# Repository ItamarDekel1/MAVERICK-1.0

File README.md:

# MAVERICK-1.0
MAVERICK 1.0: The first iteration of the flight controller, developed by Itamar Dekel, designed for drones and autonomous vehicles.

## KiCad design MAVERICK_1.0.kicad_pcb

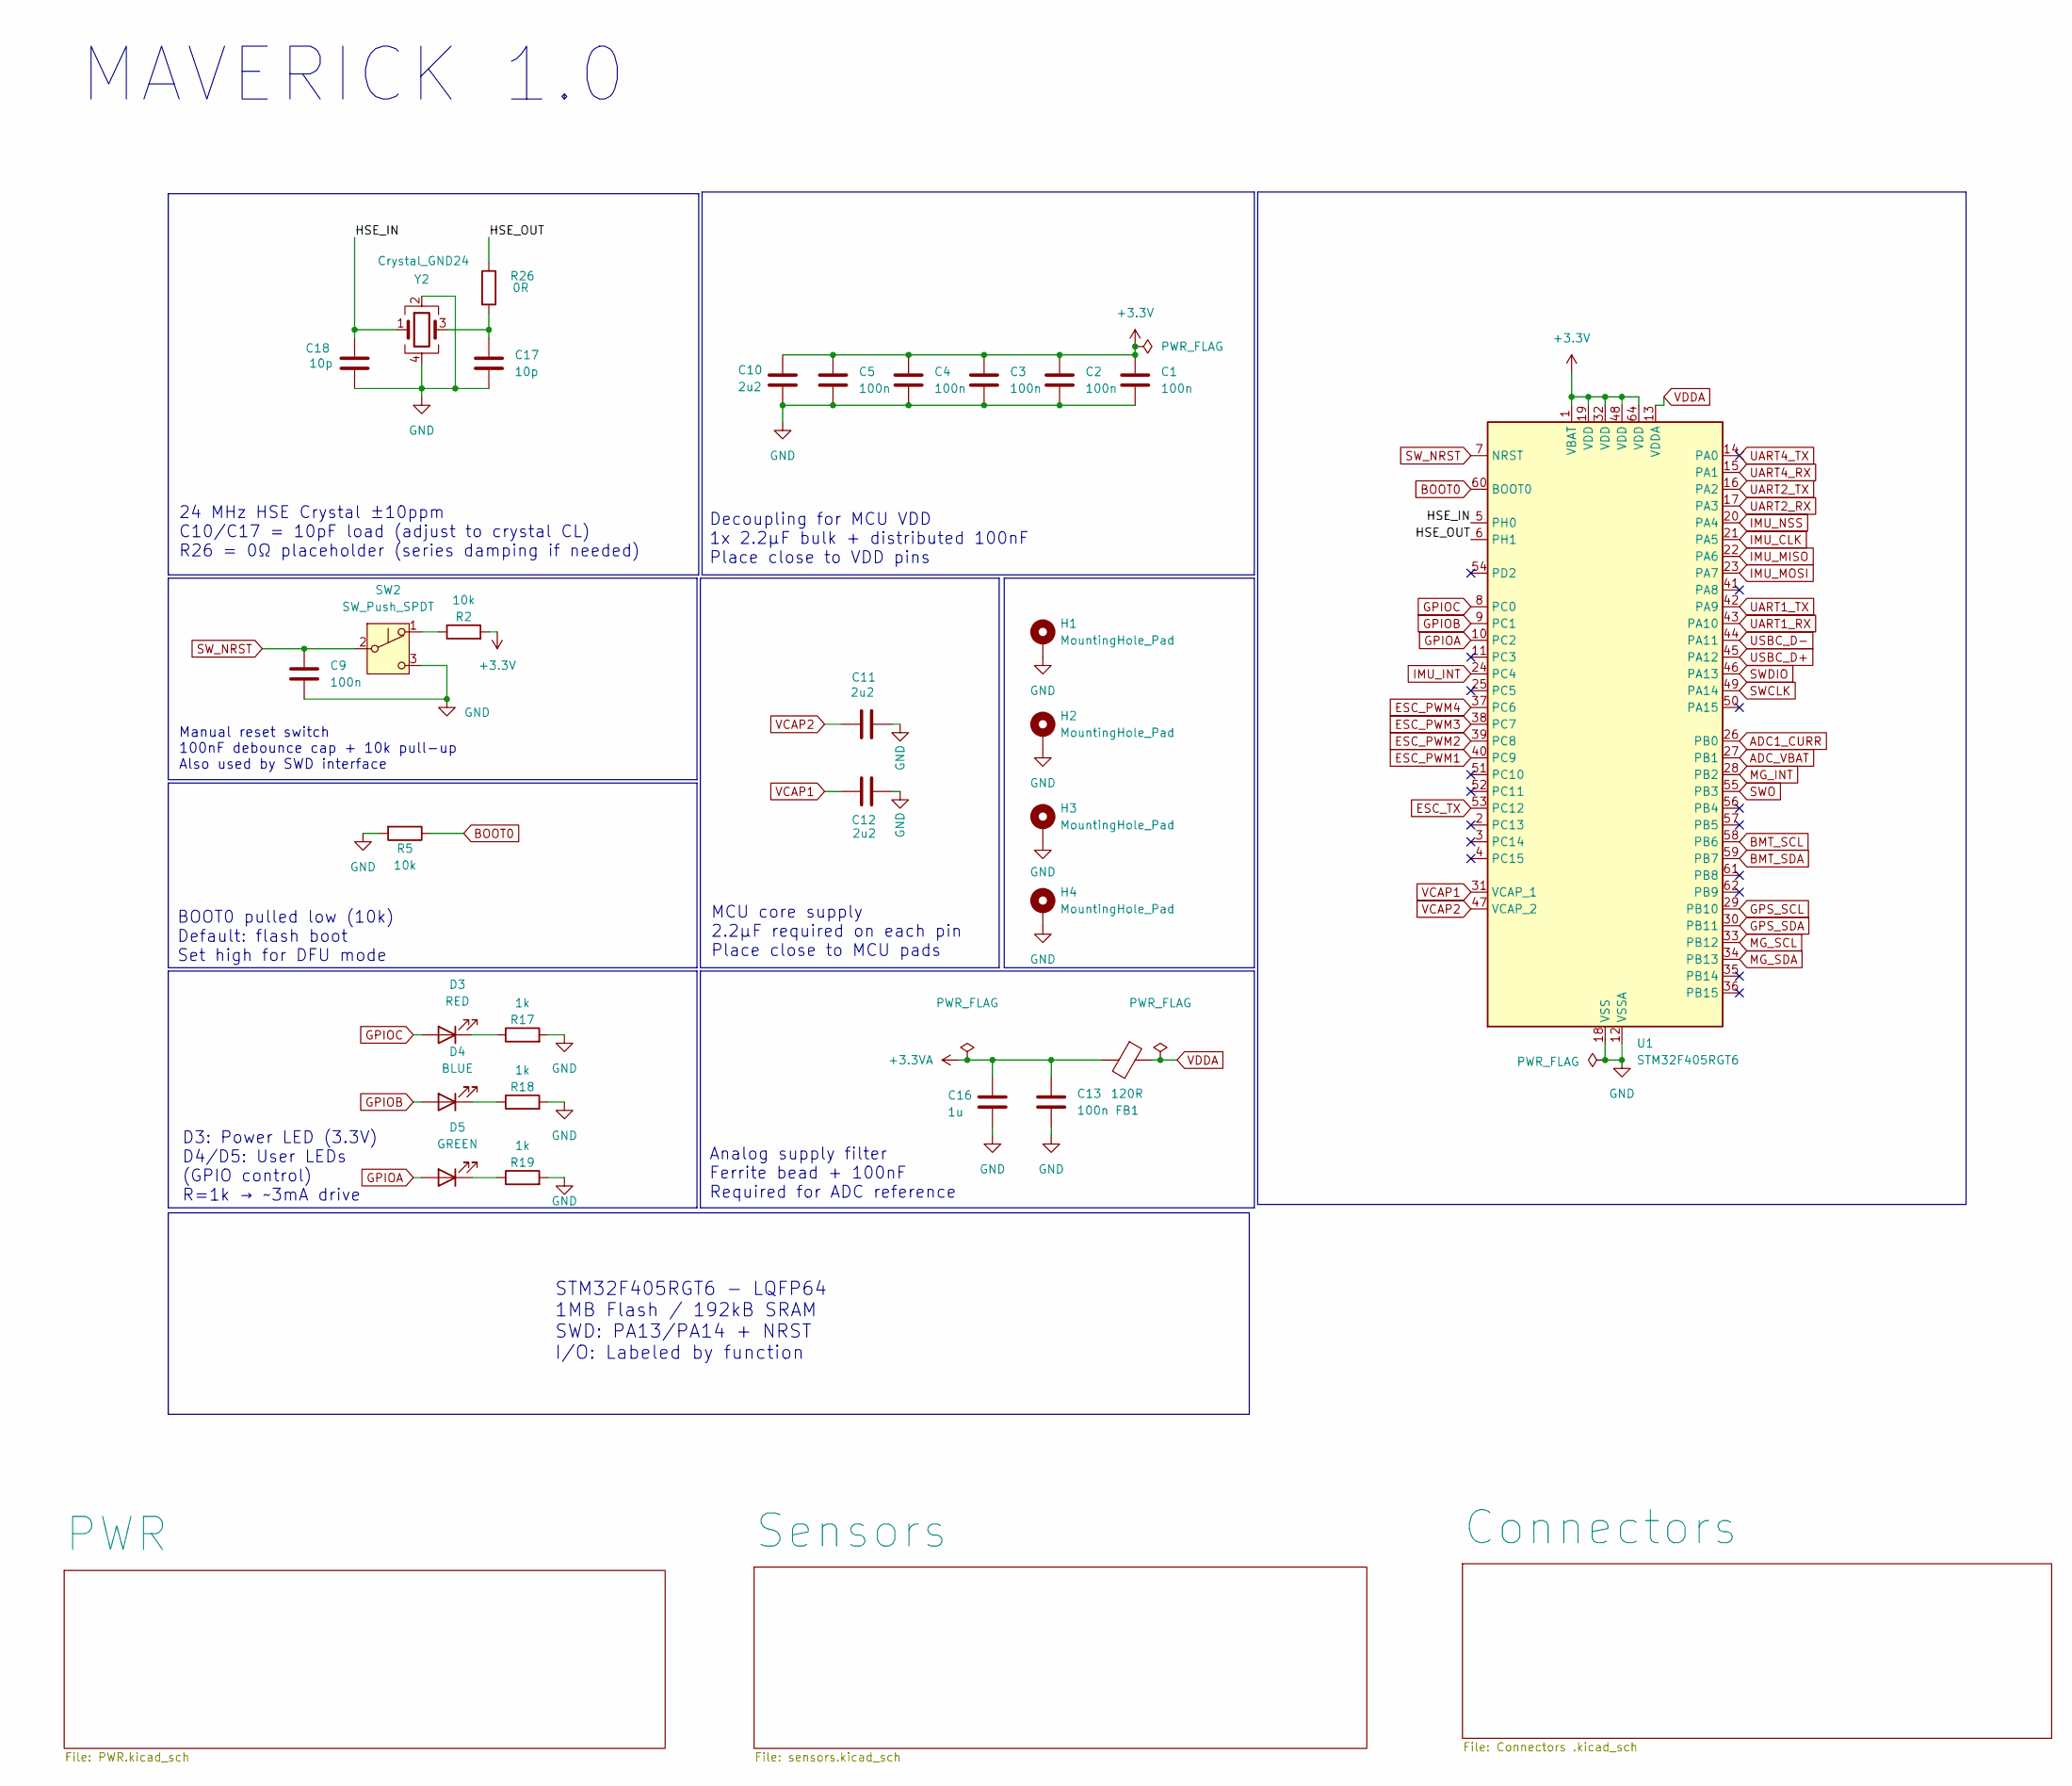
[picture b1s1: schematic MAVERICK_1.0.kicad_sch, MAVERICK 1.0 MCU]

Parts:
C1, C2, C3, C4, C5, C9, C13: 100n; C_0402_1005Metric
C10, C11, C12: 2u2; C_0603_1608Metric
C16: 1u; C_0402_1005Metric
C17, C18: 10p; C_0402_1005Metric
D3: RED; LED_0201_0603Metric
D4: BLUE; LED_0201_0603Metric
D5: GREEN; LED_0201_0603Metric
FB1: 120R; L_0402_1005Metric
H1, H2, H3, H4: MountingHole_Pad; MountingHole_2.2mm_M2_Pad_Via
R2, R5: 10k; R_0402_1005Metric
R17, R18, R19: 1k; R_0402_1005Metric
R26: 0R; R_0402_1005Metric
SW2: SW_Push_SPDT; SW_SPDT_PCM12
U1: STM32F405RGT6; LQFP-64_10x10mm_P0.5mm
Y2: Crystal_GND24; Crystal_SMD_3225-4Pin_3.2x2.5mm

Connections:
+3.3V: C1.1, C2.1, C3.1, C4.1, C5.1, C10.1, R2.2, U1.1 (VBAT), U1.19 (VDD), U1.32 (VDD), U1.48 (VDD), U1.64 (VDD); also elsewhere on the board
+3.3VA: C13.1, C16.1, FB1.2
/HSE_IN: C18.2, U1.5 (PH0), Y2.1
/HSE_OUT: R26.1, U1.6 (PH1)
ADC1_CURR: U1.26 (PB0); also elsewhere on the board
ADC_VBAT: U1.27 (PB1); also elsewhere on the board
BMT_SCL: U1.58 (PB6); also elsewhere on the board
BMT_SDA: U1.59 (PB7); also elsewhere on the board
BOOT0: R5.1, U1.60 (BOOT0)
ESC_PWM1: U1.40 (PC9); also elsewhere on the board
ESC_PWM2: U1.39 (PC8); also elsewhere on the board
ESC_PWM3: U1.38 (PC7); also elsewhere on the board
ESC_PWM4: U1.37 (PC6); also elsewhere on the board
ESC_TX: U1.53 (PC12); also elsewhere on the board
GND: C1.2, C2.2, C3.2, C4.2, C5.2, C9.1, C10.2, C11.2, C12.2, C13.2, C16.2, C17.1, C18.1, H1.1, H2.1, H3.1, H4.1, R5.2, R17.2, R18.2, R19.2, SW2.3 (C), U1.12 (VSSA), U1.18 (VSS), U1.63 (VSS), Y2.2, Y2.4; also elsewhere on the board
GPIOA: D5.2 (A), U1.10 (PC2)
GPIOB: D4.2 (A), U1.9 (PC1)
GPIOC: D3.2 (A), U1.8 (PC0)
GPS_SCL: U1.29 (PB10); also elsewhere on the board
GPS_SDA: U1.30 (PB11); also elsewhere on the board
IMU_CLK: U1.21 (PA5); also elsewhere on the board
IMU_INT: U1.24 (PC4); also elsewhere on the board
IMU_MISO: U1.22 (PA6); also elsewhere on the board
IMU_MOSI: U1.23 (PA7); also elsewhere on the board
IMU_NSS: U1.20 (PA4); also elsewhere on the board
MG_INT: U1.28 (PB2); also elsewhere on the board
MG_SCL: U1.33 (PB12); also elsewhere on the board
MG_SDA: U1.34 (PB13); also elsewhere on the board
unnamed: C17.2, R26.2, Y2.3
unnamed: D3.1 (K), R17.1
unnamed: D4.1 (K), R18.1
unnamed: D5.1 (K), R19.1
unnamed: R2.1, SW2.1 (A)
SWCLK: U1.49 (PA14); also elsewhere on the board
SWDIO: U1.46 (PA13); also elsewhere on the board
SWO: U1.55 (PB3); also elsewhere on the board
SW_NRST: C9.2, SW2.2 (B), U1.7 (NRST); also elsewhere on the board
UART1_RX: U1.43 (PA10); also elsewhere on the board
UART1_TX: U1.42 (PA9); also elsewhere on the board
UART2_RX: U1.17 (PA3); also elsewhere on the board
UART2_TX: U1.16 (PA2); also elsewhere on the board
UART4_RX: U1.15 (PA1); also elsewhere on the board
UART4_TX: U1.14 (PA0)
USBC_D+: U1.45 (PA12); also elsewhere on the board
USBC_D-: U1.44 (PA11); also elsewhere on the board
VCAP1: C12.1, U1.31 (VCAP_1)
VCAP2: C11.1, U1.47 (VCAP_2)
VDDA: FB1.1, U1.13 (VDDA)

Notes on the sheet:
STM32F405RGT6 - LQFP64 1MB Flash / 192kB SRAM SWD: PA13/PA14 + NRST I/O: Labeled by function
Manual reset switch 100nF debounce cap + 10k pull-up Also used by SWD interface
24 MHz HSE Crystal ±10ppm C10/C17 = 10pF load (adjust to crystal CL) R26 = 0Ω placeholder (series damping if needed)
MCU core supply 2.2µF required on each pin Place close to MCU pads
BOOT0 pulled low (10k) Default: flash boot Set high for DFU mode
MAVERICK 1.0
Decoupling for MCU VDD 1x 2.2µF bulk + distributed 100nF Place close to VDD pins
D3: Power LED (3.3V) D4/D5: User LEDs (GPIO control) R=1k → ~3mA drive
Analog supply filter Ferrite bead + 100nF Required for ADC reference

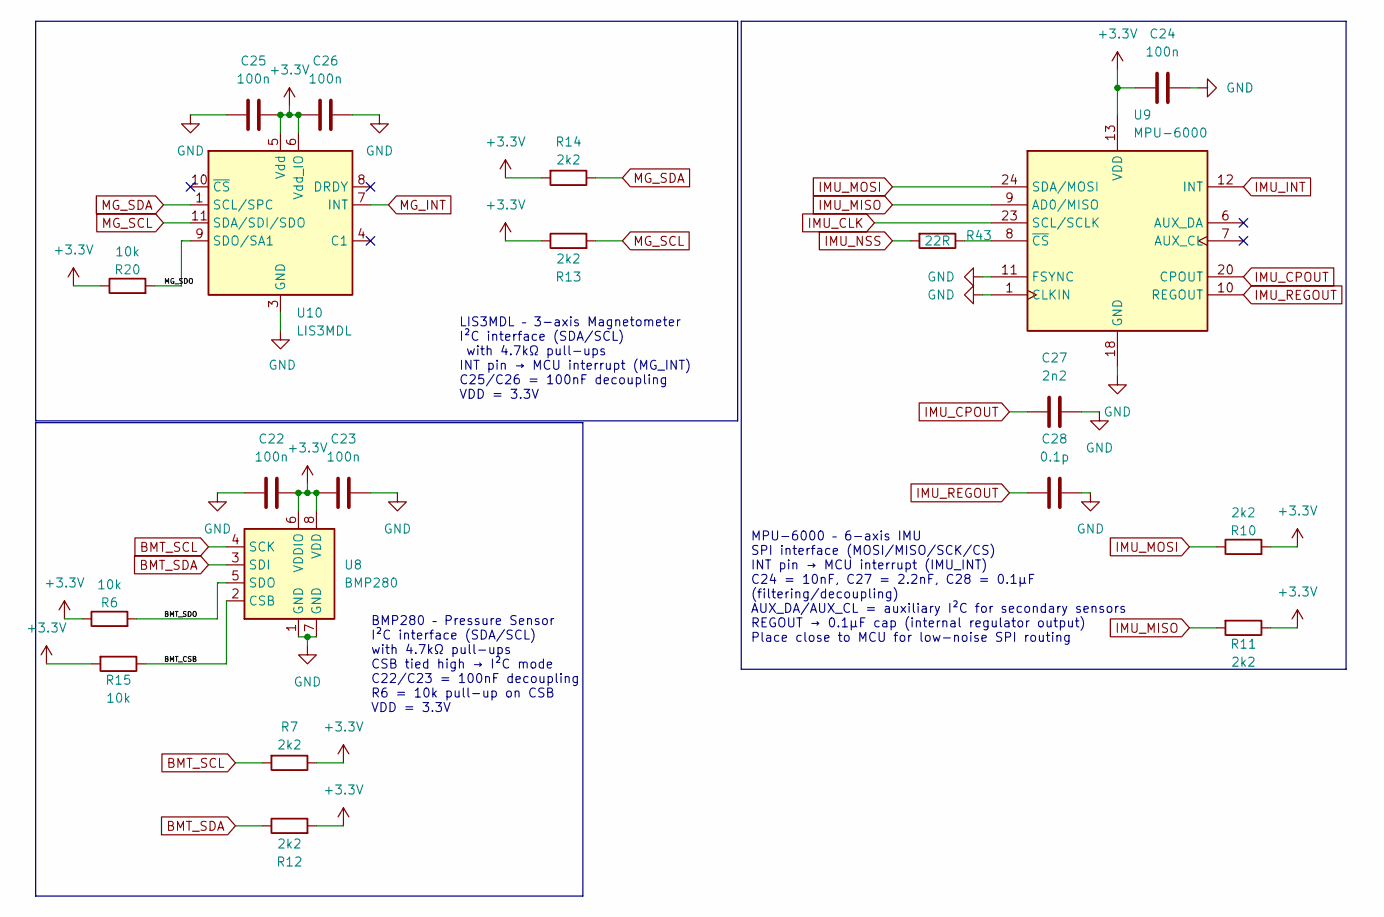
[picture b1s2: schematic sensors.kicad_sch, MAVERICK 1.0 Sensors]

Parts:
C22, C23, C24, C25, C26: 100n; C_0402_1005Metric
C27: 2n2; C_0603_1608Metric
C28: 0.1p; C_0402_1005Metric
R6, R15, R20: 10k; R_0402_1005Metric
R7, R10, R11, R12, R13, R14: 2k2; R_0402_1005Metric
R43: 22R; R_0402_1005Metric
U8: BMP280; Bosch_LGA-8_2x2.5mm_P0.65mm_ClockwisePinNumbering
U9: MPU-6000; InvenSense_QFN-24_4x4mm_P0.5mm
U10: LIS3MDL; LGA-12_2x2mm_P0.5mm

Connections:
+3.3V: C22.1, C23.2, C24.2, C25.1, C26.2, R6.1, R7.1, R10.2, R11.1, R12.2, R13.1, R14.2, R15.2, R20.1, U8.6 (VDDIO), U8.8 (VDD), U9.13 (VDD), U10.5 (Vdd), U10.6 (Vdd_IO); also elsewhere on the board
/Sensors/BMT_CSB: R15.1, U8.2 (CSB)
/Sensors/BMT_SDO: R6.2, U8.5 (SDO)
/Sensors/MG_SDO: R20.2, U10.9 (SDO/SA1)
BMT_SCL: R7.2, U8.4 (SCK); also elsewhere on the board
BMT_SDA: R12.1, U8.3 (SDI); also elsewhere on the board
GND: C22.2, C23.1, C24.1, C25.2, C26.1, C27.1, C28.1, U8.1 (GND), U8.7 (GND), U9.1 (CLKIN), U9.11 (FSYNC), U9.18 (GND), U10.2 (GND), U10.3 (GND), U10.12 (GND); also elsewhere on the board
IMU_CLK: U9.23 (SCL/SCLK); also elsewhere on the board
IMU_CPOUT: C27.2, U9.20 (CPOUT)
IMU_INT: U9.12 (INT); also elsewhere on the board
IMU_MISO: R11.2, U9.9 (AD0/MISO); also elsewhere on the board
IMU_MOSI: R10.1, U9.24 (SDA/MOSI); also elsewhere on the board
IMU_NSS: R43.2; also elsewhere on the board
IMU_REGOUT: C28.2, U9.10 (REGOUT)
MG_INT: U10.7 (INT); also elsewhere on the board
MG_SCL: R13.2, U10.11 (SDA/SDI/SDO); also elsewhere on the board
MG_SDA: R14.1, U10.1 (SCL/SPC); also elsewhere on the board
unnamed: R43.1, U9.8 (~CS)

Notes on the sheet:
MPU-6000 – 6-axis IMU SPI interface (MOSI/MISO/SCK/CS) INT pin → MCU interrupt (IMU_INT) C24 = 10nF, C27 = 2.2nF, C28 = 0.1µF (filtering/decoupling) AUX_DA/AUX_CL = auxiliary I²C for secondary sensors REGOUT → 0.1µF cap (internal regulator output) Place close to MCU for low-noise SPI routing
LIS3MDL – 3-axis Magnetometer I²C interface (SDA/SCL) with 4.7kΩ pull-ups INT pin → MCU interrupt (MG_INT) C25/C26 = 100nF decoupling VDD = 3.3V
BMP280 – Pressure Sensor I²C interface (SDA/SCL) with 4.7kΩ pull-ups CSB tied high → I²C mode C22/C23 = 100nF decoupling R6 = 10k pull-up on CSB VDD = 3.3V

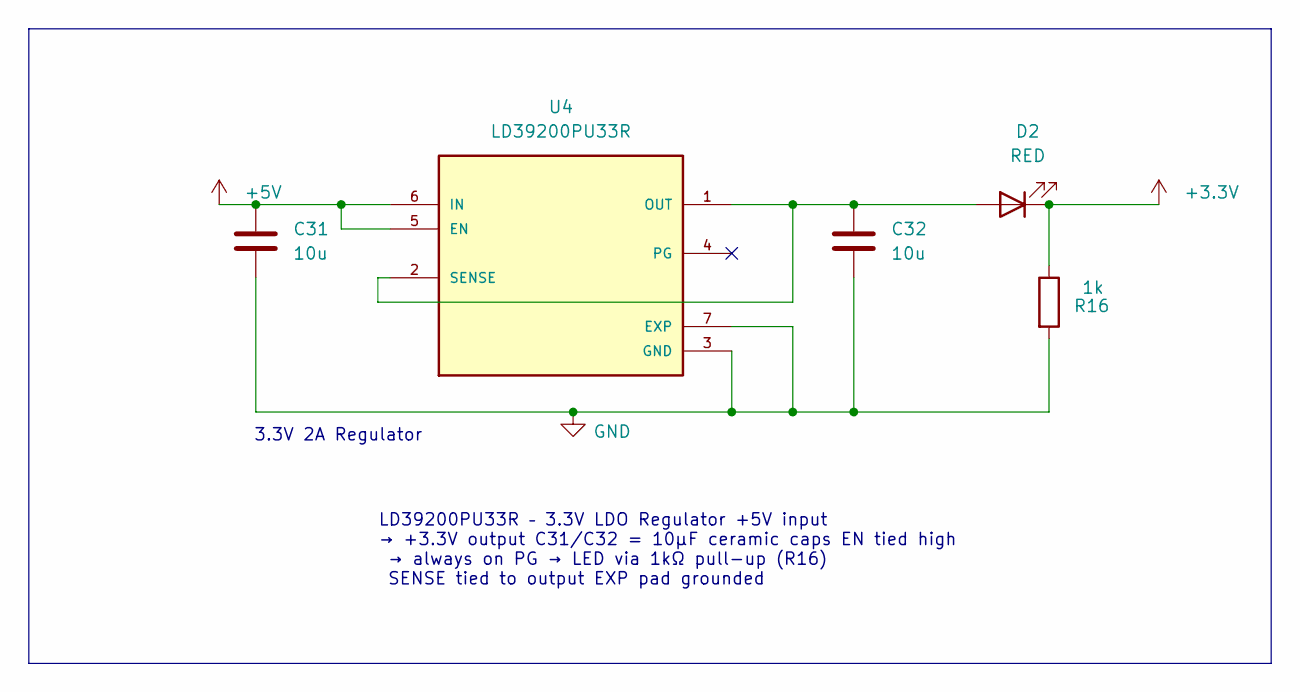
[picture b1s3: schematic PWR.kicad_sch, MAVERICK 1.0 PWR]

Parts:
C31, C32: 10u; C_0603_1608Metric
D2: RED; LED_0201_0603Metric
R16: 1k; R_0402_1005Metric
U4: LD39200PU33R; SON95P300X300X100-7N; PARTREV 3

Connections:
+3.3V: D2.1 (K), R16.1; also elsewhere on the board
+5V: C31.1, U4.5 (EN), U4.6 (IN); also elsewhere on the board
GND: C31.2, C32.2, R16.2, U4.3 (GND), U4.7 (EXP); also elsewhere on the board
unnamed: C32.1, D2.2 (A), U4.1 (OUT), U4.2 (SENSE)

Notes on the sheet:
3.3V 2A Regulator
LD39200PU33R – 3.3V LDO Regulator +5V input → +3.3V output C31/C32 = 10µF ceramic caps EN tied high → always on PG → LED via 1kΩ pull-up (R16) SENSE tied to output EXP pad grounded

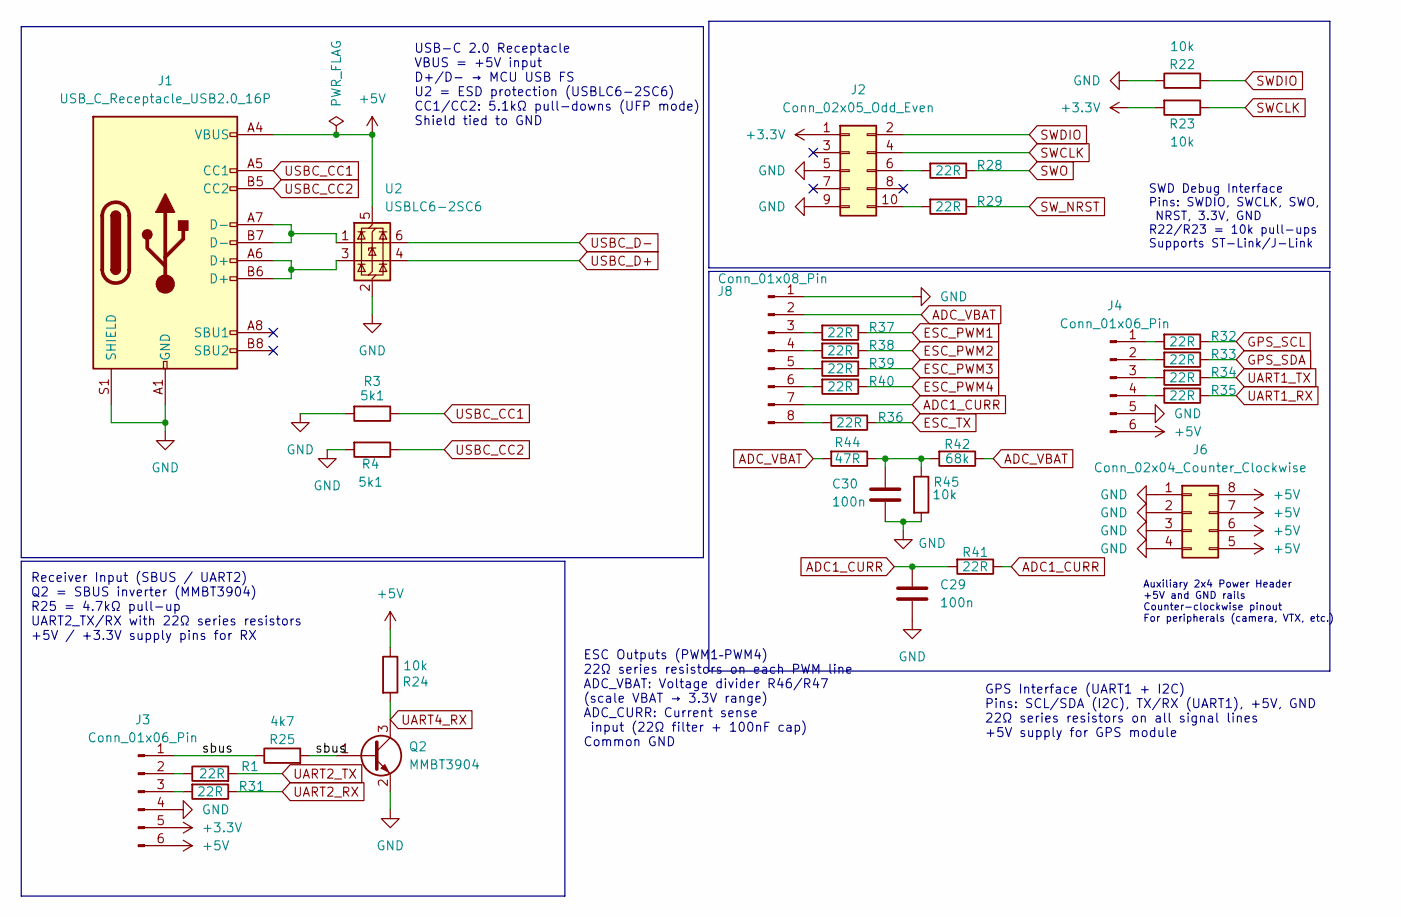
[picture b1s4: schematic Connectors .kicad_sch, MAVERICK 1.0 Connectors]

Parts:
C29, C30: 100n; C_0402_1005Metric
J1: USB_C_Receptacle_USB2.0_16P; USB_C_Receptacle_GCT_USB4105-xx-A_16P_TopMnt_Horizontal
J2: Conn_02x05_Odd_Even; PinHeader_2x05_P1.00mm_Horizontal
J3, J4: Conn_01x06_Pin; CONN_SM06B-SRSS-TB_JST
J6: Conn_02x04_Counter_Clockwise; PinHeader_2x04_P1.00mm_Horizontal
J8: Conn_01x08_Pin; JST_SM08B-SRSS-TB
Q2: MMBT3904; SOT-23
R1, R28, R29, R31, R32, R33, R34, R35, R36, R37, R38, R39, R40, R41: 22R; R_0402_1005Metric
R3, R4: 5k1; R_0402_1005Metric
R22, R23, R24, R45: 10k; R_0402_1005Metric
R25: 4k7; R_0402_1005Metric
R42: 68k; R_0402_1005Metric
R44: 47R; R_0402_1005Metric
U2: USBLC6-2SC6; SOT-23-6

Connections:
+3.3V: J2.1, J3.5, R23.2; also elsewhere on the board
+5V: J1.A4 (VBUS), J1.A9 (VBUS), J1.B4 (VBUS), J1.B9 (VBUS), J3.6, J4.6, J6.5, J6.6, J6.7, J6.8, R24.1, U2.5 (VBUS); also elsewhere on the board
/Connectors/sbus: J3.1, Q2.1 (B), R25.1, R25.2
ADC1_CURR: C29.2, J8.7, R41.1, R41.2; also elsewhere on the board
ADC_VBAT: J8.2, R42.1, R44.2; also elsewhere on the board
ESC_PWM1: R37.1; also elsewhere on the board
ESC_PWM2: R38.1; also elsewhere on the board
ESC_PWM3: R39.1; also elsewhere on the board
ESC_PWM4: R40.1; also elsewhere on the board
ESC_TX: R36.1; also elsewhere on the board
GND: C29.1, C30.1, J1.A1 (GND), J1.A12 (GND), J1.B1 (GND), J1.B12 (GND), J1.S1 (SHIELD), J2.5, J2.9, J3.4, J4.5, J6.1, J6.2, J6.3, J6.4, J8.1, Q2.2 (E), R3.2, R4.2, R22.1, R45.2, U2.2 (GND); also elsewhere on the board
GPS_SCL: R32.1; also elsewhere on the board
GPS_SDA: R33.1; also elsewhere on the board
unnamed: C30.2, R42.2, R44.1, R45.1
unnamed: J1.A6 (D+), J1.B6 (D+), U2.3 (I/O2)
unnamed: J1.A7 (D-), J1.B7 (D-), U2.1 (I/O1)
unnamed: J2.6, R28.2
unnamed: J2.10, R29.2
unnamed: J3.2, R1.1
unnamed: J3.3, R31.2
unnamed: J4.1, R32.2
unnamed: J4.2, R33.2
unnamed: J4.3, R34.2
unnamed: J4.4, R35.2
unnamed: J8.3, R37.2
unnamed: J8.4, R38.2
unnamed: J8.5, R39.2
unnamed: J8.6, R40.2
unnamed: J8.8, R36.2
SWCLK: J2.4, R23.1; also elsewhere on the board
SWDIO: J2.2, R22.2; also elsewhere on the board
SWO: R28.1; also elsewhere on the board
SW_NRST: R29.1; also elsewhere on the board
UART1_RX: R35.1; also elsewhere on the board
UART1_TX: R34.1; also elsewhere on the board
UART2_RX: R31.1; also elsewhere on the board
UART2_TX: R1.2; also elsewhere on the board
UART4_RX: Q2.3 (C), R24.2; also elsewhere on the board
USBC_CC1: J1.A5 (CC1), R3.1
USBC_CC2: J1.B5 (CC2), R4.1
USBC_D+: U2.4 (I/O2); also elsewhere on the board
USBC_D-: U2.6 (I/O1); also elsewhere on the board

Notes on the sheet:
GPS Interface (UART1 + I2C) Pins: SCL/SDA (I2C), TX/RX (UART1), +5V, GND 22Ω series resistors on all signal lines +5V supply for GPS module
SWD Debug Interface Pins: SWDIO, SWCLK, SWO, NRST, 3.3V, GND R22/R23 = 10k pull-ups Supports ST-Link/J-Link
ESC Outputs (PWM1–PWM4) 22Ω series resistors on each PWM line ADC_VBAT: Voltage divider R46/R47 (scale VBAT → 3.3V range) ADC_CURR: Current sense input (22Ω filter + 100nF cap) Common GND
Receiver Input (SBUS / UART2) Q2 = SBUS inverter (MMBT3904) R25 = 4.7kΩ pull-up UART2_TX/RX with 22Ω series resistors +5V / +3.3V supply pins for RX
USB-C 2.0 Receptacle VBUS = +5V input D+/D- → MCU USB FS U2 = ESD protection (USBLC6-2SC6) CC1/CC2: 5.1kΩ pull-downs (UFP mode) Shield tied to GND
Auxiliary 2x4 Power Header +5V and GND rails Counter-clockwise pinout For peripherals (camera, VTX, etc.)

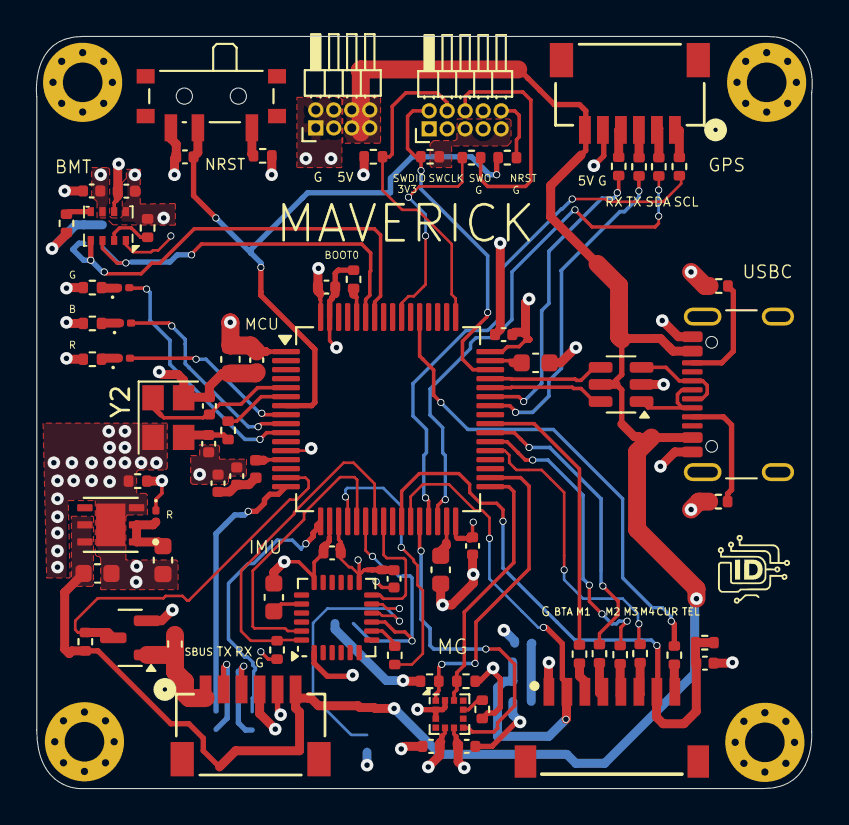
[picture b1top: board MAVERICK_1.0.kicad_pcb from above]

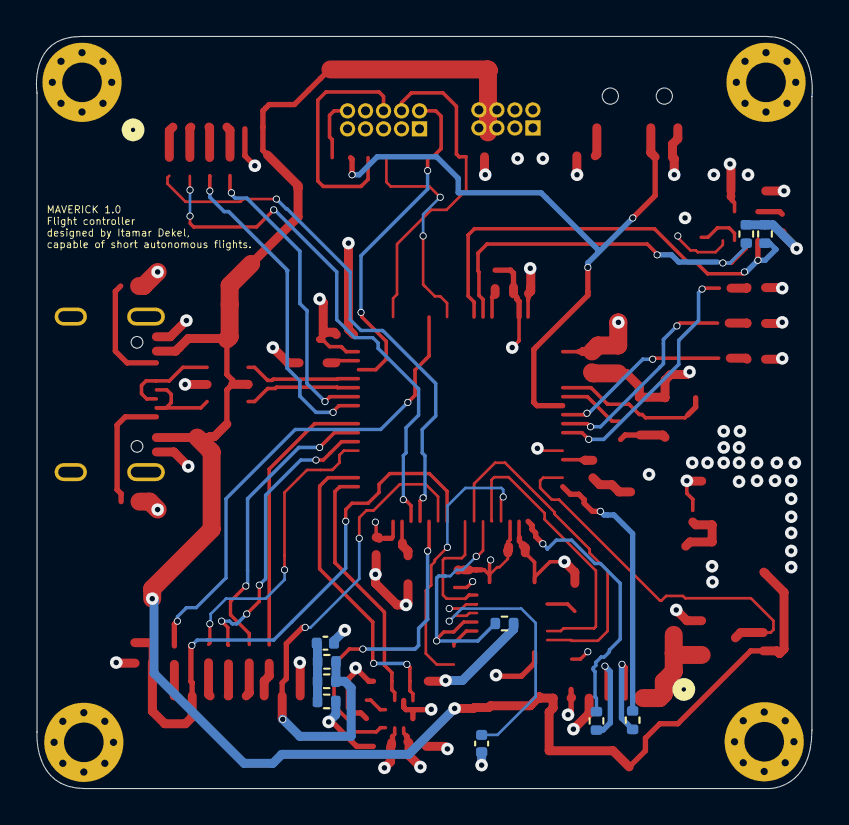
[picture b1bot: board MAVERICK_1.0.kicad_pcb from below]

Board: 4 copper layers, 43.1 x 41.8 mm, 88 parts (10 on the bottom side), 74 nets.
